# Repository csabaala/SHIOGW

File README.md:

# [SHIOGW](/Hardware/SHIOGW)

DIN rail mount extension board for [Olimex ESP32-GATEWAY](https://www.olimex.com/Products/IoT/ESP32/ESP32-GATEWAY/open-source-hardware).

More [Pictures](/Pictures#assembled-boards) and [Video](https://youtu.be/ds2y22MUNzQ) of the assembled board and extensions.

Example [ESPHome configs](/ESPHome)

## Features

* 12V to 5V step-down converter
* 2 open collector output (50 mA load per channel)
* 2 opto isolated input
* LEDs for output and input status
* 2 sensor input (ds18b20, dht)
* RS-485 interface
* 4 pin JST connector for I2C extensions
* 14 pin IDC connector for direct GPIO access

View [3D model](https://3dviewer.net/#model=https://github.com/csabaala/SHIOGW/blob/main/Hardware/SHIOGW/SHIOGW.wrl)

## Extensions

### [GWHMI](/Hardware/GWHMI)

Control interface for SHIOGW.

* PCB for 128x64 OLED display and control buttons. Fits the 0.96 and 1.3 inch OLED versions.
* Mountable top of the SHIOGW board.
* Connects to SHIOGW's 12 pin IDC connector with a small ribbon cable.
* BTN1 (up) and BTN3 (down) shared with I1 and I2 on SHIOGW main board.

View [3D model](https://3dviewer.net/#model=https://github.com/csabaala/SHIOGW/blob/main/Hardware/GWHMI/GWHMI.wrl)

### [SHIO88E](/Hardware/SHIO88E)

I2C IO extension.

* MCP23017 based
* 8 open collector output (50 mA load per channel)
* 8 opto isolated input
* LEDs for output and input status
* One more I2C connector to connect other device

View [3D model](https://3dviewer.net/#https://github.com/csabaala/SHIOGW/blob/main/Hardware/SHIO88E/SHIO88E.wrl)

### [LRMNT](/Hardware/LRMNT)

Adapter PCB to mount [Heltec LoRa 32 V3](https://heltec.org/project/wifi-lora-32-v3/) module to SHIOGW board.

* 2 extra open collector output (50 mA load per channel)
* 4 extra opto isolated input

View [3D model](https://3dviewer.net/#https://github.com/csabaala/SHIOGW/blob/main/Hardware/LRMNT/LRMNT.wrl)

### [SHIOADS](/Hardware/SHIOADS)

Din rail mount breakout board for ADS1115 module.

* On board voltage divider resistors (R1 - R8)
* Solder jumpers to set I2C address (JP1 - JP4)

View [3D model](https://3dviewer.net/#https://github.com/csabaala/SHIOGW/blob/main/Hardware/SHIOADS/SHIOADS.wrl)

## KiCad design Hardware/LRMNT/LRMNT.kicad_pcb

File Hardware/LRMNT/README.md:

# Assembly information
## 12V power source
To activate the additional digital input and output channels, connect the power source to the H5 header.
You can connect to the SHIOGW H10 connector using a JST cable.

## Using input channel as ADC
You can soldering the input channels (I3 - I5) to use as ADC (Analog to Digital Converter) input.
To enable ADC reading solder the following parts (for example for I3 channel):

* R1: 0 ohm
* R5: 0 ohm (to bypass OP1)
* R3: Voltage divider high resistor 
* R4: Voltage divider low resistor 
* C5: 100 nF capacitor

Do not solder:

* OP1
* C1

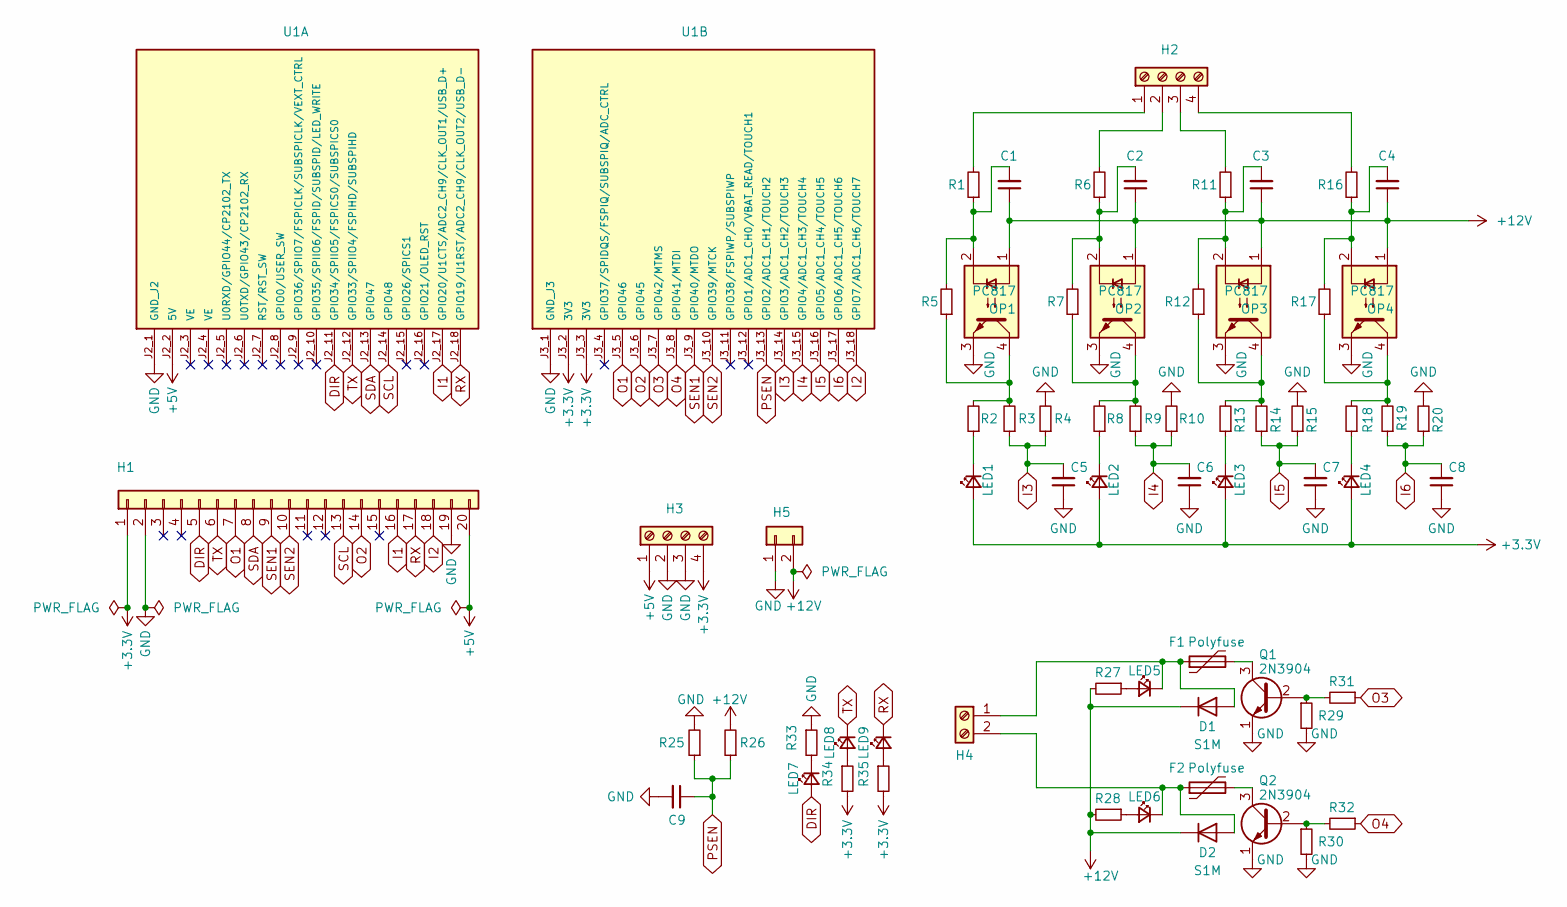
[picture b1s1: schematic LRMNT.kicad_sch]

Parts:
C1, C2, C3, C4: C_Small; C_0805_2012Metric_Pad1.18x1.45mm_HandSolder; LCSC C1710
C5, C6, C7, C8, C9: C_Small; C_0805_2012Metric_Pad1.18x1.45mm_HandSolder; LCSC C49678
D1, D2: S1M; D_SMA; LCSC C412437
F1, F2: Polyfuse; Fuse_1206_3216Metric_Pad1.42x1.75mm_HandSolder; LCSC C2830235
H1: Conn_01x20; PinHeader_1x20_P2.54mm_Vertical
H2, H3: Screw_Terminal_01x04; PhoenixContact_MCV_1,5_4-G-3.5_1x04_P3.50mm_Vertical
H4: Screw_Terminal_01x02; PhoenixContact_MCV_1,5_2-G-3.5_1x02_P3.50mm_Vertical
H5: Conn_01x02; PinHeader_1x02_P2.54mm_Vertical
LED1, LED2, LED3, LED4, LED5, LED6: LED_Small; LED_0805_2012Metric_Pad1.15x1.40mm_HandSolder; LCSC C84256
LED7, LED8: LED_Small; LED_0805_2012Metric_Pad1.15x1.40mm_HandSolder; LCSC C2297
LED9: LED_Small; LED_0805_2012Metric_Pad1.15x1.40mm_HandSolder; LCSC C2296
OP1, OP2, OP3, OP4: PC817; PC817_custom
Q1, Q2: 2N3904; TO-92_HandSolder
R1, R2, R6, R8, R11, R13, R16, R18, R19, R25, R26: R_Small; R_0805_2012Metric_Pad1.20x1.40mm_HandSolder; LCSC C17520
R3, R4, R5, R7, R9, R10, R12, R14, R15, R17, R20: R_Small; R_0805_2012Metric_Pad1.20x1.40mm_HandSolder
R27, R28, R29, R30, R33, R34, R35: R_Small; R_0805_2012Metric_Pad1.20x1.40mm_HandSolder; LCSC C17414
R31, R32: R_Small; R_0805_2012Metric_Pad1.20x1.40mm_HandSolder; LCSC C17513
U1: WIFI_KIT_32__V3_; MODULE_WIFI_KIT_32__V3_; PARTREV Rev 1.1

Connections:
+3.3V: H1.1, H3.4, LED1.2 (A), LED2.2 (A), LED3.2 (A), LED4.2 (A), R34.2, R35.2, U1.J3_2 (3V3), U1.J3_3 (3V3)
+5V: H1.20, H3.1, U1.J2_2 (5V)
+12V: C1.1, C2.1, C3.1, C4.1, D1.1 (K), D2.1 (K), H5.2, OP1.1, OP2.1, OP3.1, OP4.1, R26.2, R27.2, R28.2
DIR: H1.5, LED7.2 (A), U1.J2_11 (GPIO34/SPIIO5/FSPICS0/SUBSPICS0)
GND: C5.1, C6.1, C7.1, C8.1, C9.2, H1.2, H1.19, H3.2, H3.3, H5.1, OP1.3, OP2.3, OP3.3, OP4.3, Q1.1 (E), Q2.1 (E), R4.2, R10.2, R15.2, R20.2, R25.2, R29.2, R30.2, R33.1, U1.J2_1 (GND_J2), U1.J3_1 (GND_J3); also elsewhere on the board
I1: H1.16, U1.J2_17 (GPIO20/U1CTS/ADC2_CH9/CLK_OUT1/USB_D+)
I2: H1.18, U1.J3_18 (GPIO7/ADC1_CH6/TOUCH7)
I3: C5.2, R3.1, R4.1, U1.J3_14 (GPIO3/ADC1_CH2/TOUCH3)
I4: C6.2, R9.1, R10.1, U1.J3_15 (GPIO4/ADC1_CH3/TOUCH4)
I5: C7.2, R14.1, R15.1, U1.J3_16 (GPIO5/ADC1_CH4/TOUCH5)
I6: C8.2, R19.1, R20.1, U1.J3_17 (GPIO6/ADC1_CH5/TOUCH6)
unnamed: C1.2, OP1.2, R1.1, R5.2
unnamed: C2.2, OP2.2, R6.1, R7.2
unnamed: C3.2, OP3.2, R11.1, R12.2
unnamed: C4.2, OP4.2, R16.1, R17.2
unnamed: D1.2 (A), F1.1, H4.1, LED5.1 (K)
unnamed: D2.2 (A), F2.1, H4.2, LED6.1 (K)
unnamed: H2.1, R1.2
unnamed: H2.2, R6.2
unnamed: H2.3, R11.2
unnamed: H2.4, R16.2
unnamed: LED1.1 (K), R2.1
unnamed: LED2.1 (K), R8.1
unnamed: LED3.1 (K), R13.1
unnamed: LED4.1 (K), R18.1
unnamed: LED5.2 (A), R27.1
unnamed: LED6.2 (A), R28.1
unnamed: LED7.1 (K), R33.2
unnamed: LED8.2 (A), R34.1
unnamed: LED9.2 (A), R35.1
unnamed: OP1.4, R2.2, R3.2, R5.1
unnamed: OP2.4, R7.1, R8.2, R9.2
unnamed: OP3.4, R12.1, R13.2, R14.2
unnamed: OP4.4, R17.1, R18.2, R19.2
unnamed: Q1.2 (B), R29.1, R31.2
unnamed: F1.2, Q1.3 (C)
unnamed: Q2.2 (B), R30.1, R32.2
unnamed: F2.2, Q2.3 (C)
O1: H1.7, U1.J3_5 (GPIO46)
O2: H1.14, U1.J3_6 (GPIO45)
O3: R31.1, U1.J3_7 (GPIO42/MTMS)
O4: R32.1, U1.J3_8 (GPIO41/MTDI)
PSEN: C9.1, R25.1, R26.1, U1.J3_13 (GPIO2/ADC1_CH1/TOUCH2)
RX: H1.17, LED9.1 (K), U1.J2_18 (GPIO19/U1RST/ADC2_CH9/CLK_OUT2/USB_D-)
SCL: H1.13, U1.J2_14 (GPIO48)
SDA: H1.8, U1.J2_13 (GPIO47)
SEN1: H1.9, U1.J3_9 (GPIO40/MTDO)
SEN2: H1.10, U1.J3_10 (GPIO39/MTCK)
TX: H1.6, LED8.1 (K), U1.J2_12 (GPIO33/SPIIO4/FSPIHD/SUBSPIHD)

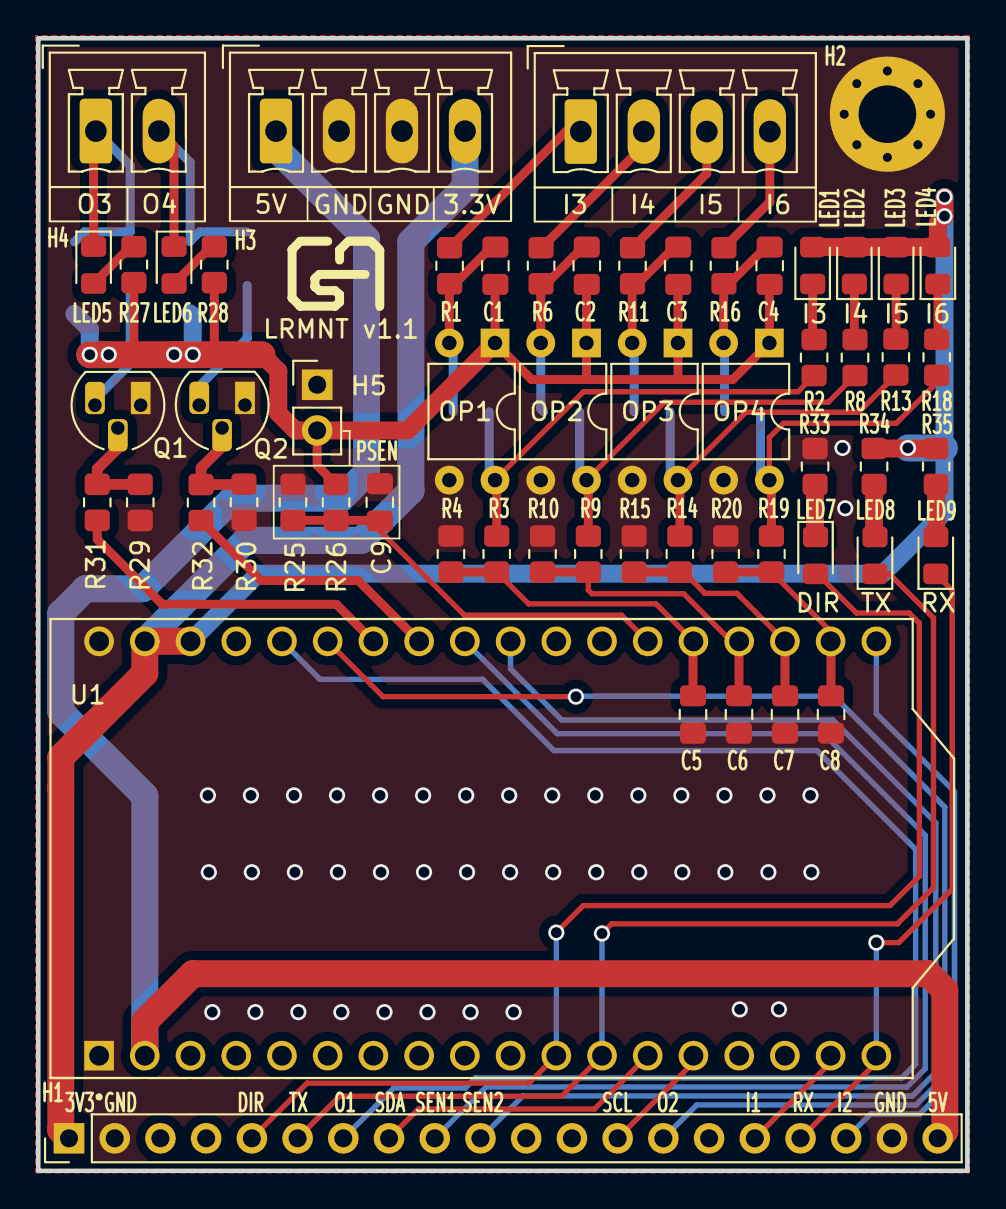
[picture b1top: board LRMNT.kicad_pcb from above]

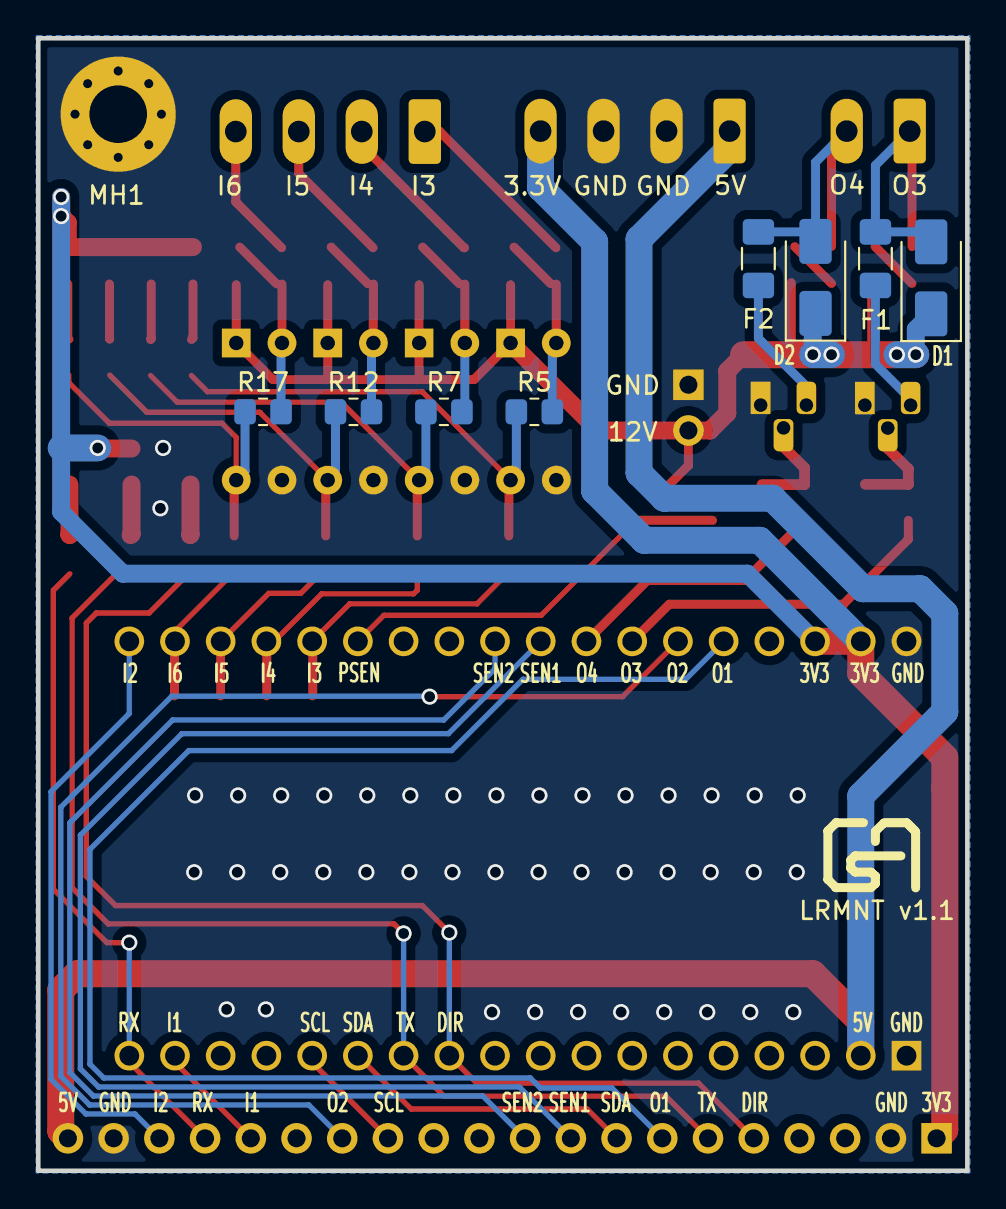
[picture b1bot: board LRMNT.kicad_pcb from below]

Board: 2 copper layers, 51.6 x 62.9 mm, 66 parts (8 on the bottom side), 49 nets.

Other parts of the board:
MH1: MountingHole_Pad; MountingHole_3.2mm_M3_Pad_Via

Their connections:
GND: MH1.1; also elsewhere on the board

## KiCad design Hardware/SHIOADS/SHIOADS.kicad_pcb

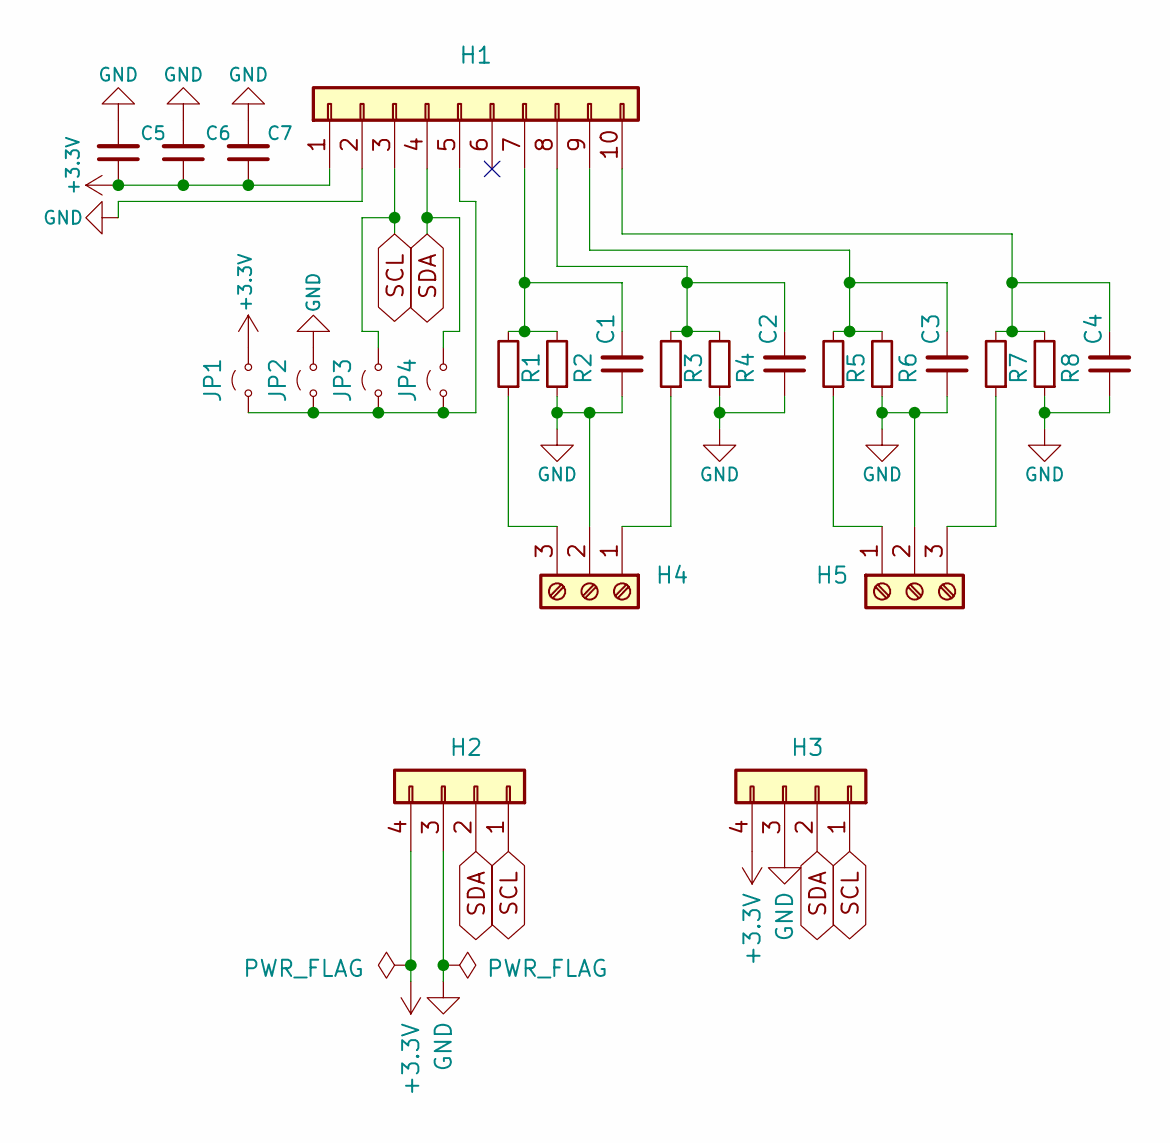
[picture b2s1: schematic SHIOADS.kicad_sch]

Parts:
C1, C2, C3, C4: C_Small; C_0805_2012Metric_Pad1.18x1.45mm_HandSolder; LCSC C1710
C5, C6: C_Small; C_1206_3216Metric_Pad1.33x1.80mm_HandSolder; LCSC C50254
C7: C_Small; C_0805_2012Metric_Pad1.18x1.45mm_HandSolder; LCSC C49678
H1: Conn_01x10; PinSocket_1x10_P2.54mm_Vertical
H2, H3: Conn_01x04; JST_XH_B4B-XH-A_1x04_P2.50mm_Vertical
H4, H5: Screw_Terminal_01x03; TerminalBlock_MSTB 2,5 3-G-5,08_v3
JP1, JP2, JP3, JP4: Jumper_2_Small_Open; SolderJumper-2_P1.3mm_Open_RoundedPad1.0x1.5mm
R1, R3, R5, R7: R_Small; R_0805_2012Metric_Pad1.20x1.40mm_HandSolder; LCSC C17414
R2, R4, R6, R8: R_Small; R_0805_2012Metric_Pad1.20x1.40mm_HandSolder; LCSC C17513

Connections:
+3.3V: C5.1, C6.1, C7.1, H1.1, H2.4, H3.4, JP1.2 (B)
GND: C1.1, C2.1, C3.1, C4.1, C5.2, C6.2, C7.2, H1.2, H2.3, H3.3, H4.2, H5.2, JP2.2 (B), R2.1, R4.1, R6.1, R8.1
unnamed: H1.5, JP1.1 (A), JP2.1 (A), JP3.1 (A), JP4.1 (A)
unnamed: C1.2, H1.7, R1.2, R2.2
unnamed: C2.2, H1.8, R3.2, R4.2
unnamed: C3.2, H1.9, R5.2, R6.2
unnamed: C4.2, H1.10, R7.2, R8.2
unnamed: H4.1, R3.1
unnamed: H4.3, R1.1
unnamed: H5.1, R5.1
unnamed: H5.3, R7.1
SCL: H1.3, H2.1, H3.1, JP3.2 (B)
SDA: H1.4, H2.2, H3.2, JP4.2 (B)

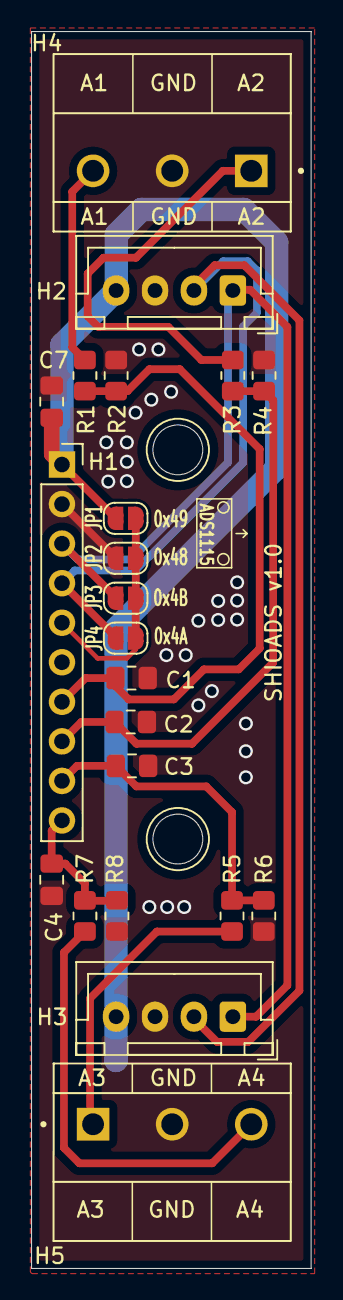
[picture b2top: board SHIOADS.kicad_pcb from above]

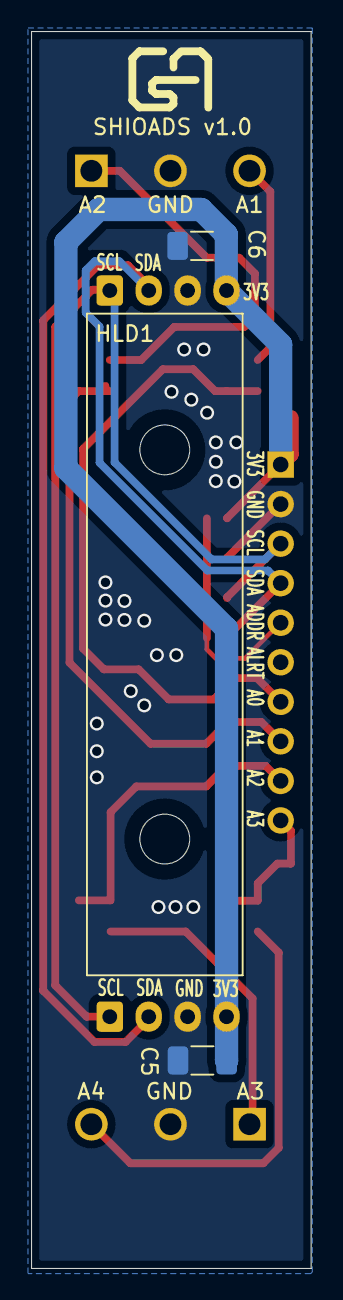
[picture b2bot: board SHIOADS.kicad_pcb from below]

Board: 2 copper layers, 18.0 x 79.5 mm, 25 parts (2 on the bottom side), 13 nets.

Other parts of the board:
HLD1: DINRailAdapter_3xM3_PhoenixContact_1201578

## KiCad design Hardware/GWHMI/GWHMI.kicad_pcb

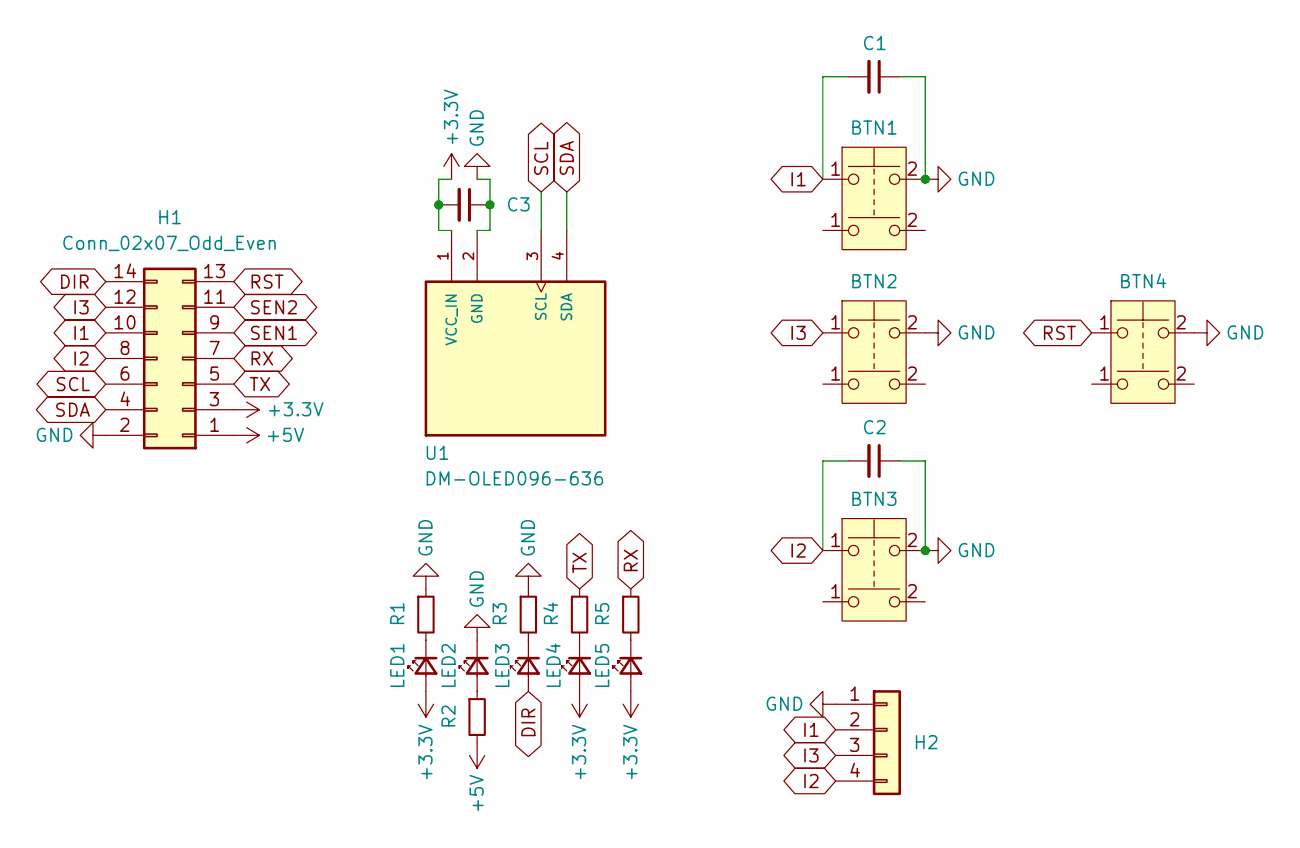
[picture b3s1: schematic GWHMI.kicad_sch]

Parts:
BTN1, BTN2, BTN3, BTN4: SW_Push_Dual; SW_SPST_PTS645_handsolder
C1, C2, C3: C_Small; C_0805_2012Metric_Pad1.18x1.45mm_HandSolder; LCSC C49678
H1: Conn_02x07_Odd_Even; PinHeader_2x07_P2.54mm_Vertical
H2: Conn_01x04; PinHeader_1x04_P2.54mm_Vertical
LED1, LED5: LED_Small; LED_0805_2012Metric_Pad1.15x1.40mm_HandSolder; LCSC C2296
LED2: LED_Small; LED_0805_2012Metric_Pad1.15x1.40mm_HandSolder; LCSC C84256
LED3, LED4: LED_Small; LED_0805_2012Metric_Pad1.15x1.40mm_HandSolder; LCSC C2297
R1: R_Small; R_0805_2012Metric_Pad1.20x1.40mm_HandSolder; LCSC C17520
R2: R_Small; R_0805_2012Metric_Pad1.20x1.40mm_HandSolder; LCSC C17661
R3, R4, R5: R_Small; R_0805_2012Metric_Pad1.20x1.40mm_HandSolder; LCSC C17414
U1: DM-OLED096-636; display_oled_128x64_i2c; PARTREV 2018-09-10

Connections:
+3.3V: C3.2, H1.3, LED1.2 (A), LED4.2 (A), LED5.2 (A), U1.1 (VCC_IN)
+5V: H1.1, R2.2
DIR: H1.14, LED3.2 (A)
GND: BTN1.2, BTN2.2, BTN3.2, BTN4.2, C1.1, C2.1, C3.1, H1.2, H2.1, LED2.1 (K), R1.1, R3.1, U1.2 (GND)
I1: BTN1.1, C1.2, H1.10, H2.2
I2: BTN3.1, C2.2, H1.8, H2.4
I3: BTN2.1, H1.12, H2.3
unnamed: LED1.1 (K), R1.2
unnamed: LED2.2 (A), R2.1
unnamed: LED3.1 (K), R3.2
unnamed: LED4.1 (K), R4.2
unnamed: LED5.1 (K), R5.2
RST: BTN4.1, H1.13
RX: H1.7, R5.1
SCL: H1.6, U1.3 (SCL)
SDA: H1.4, U1.4 (SDA)
SEN1: H1.9
SEN2: H1.11
TX: H1.5, R4.1

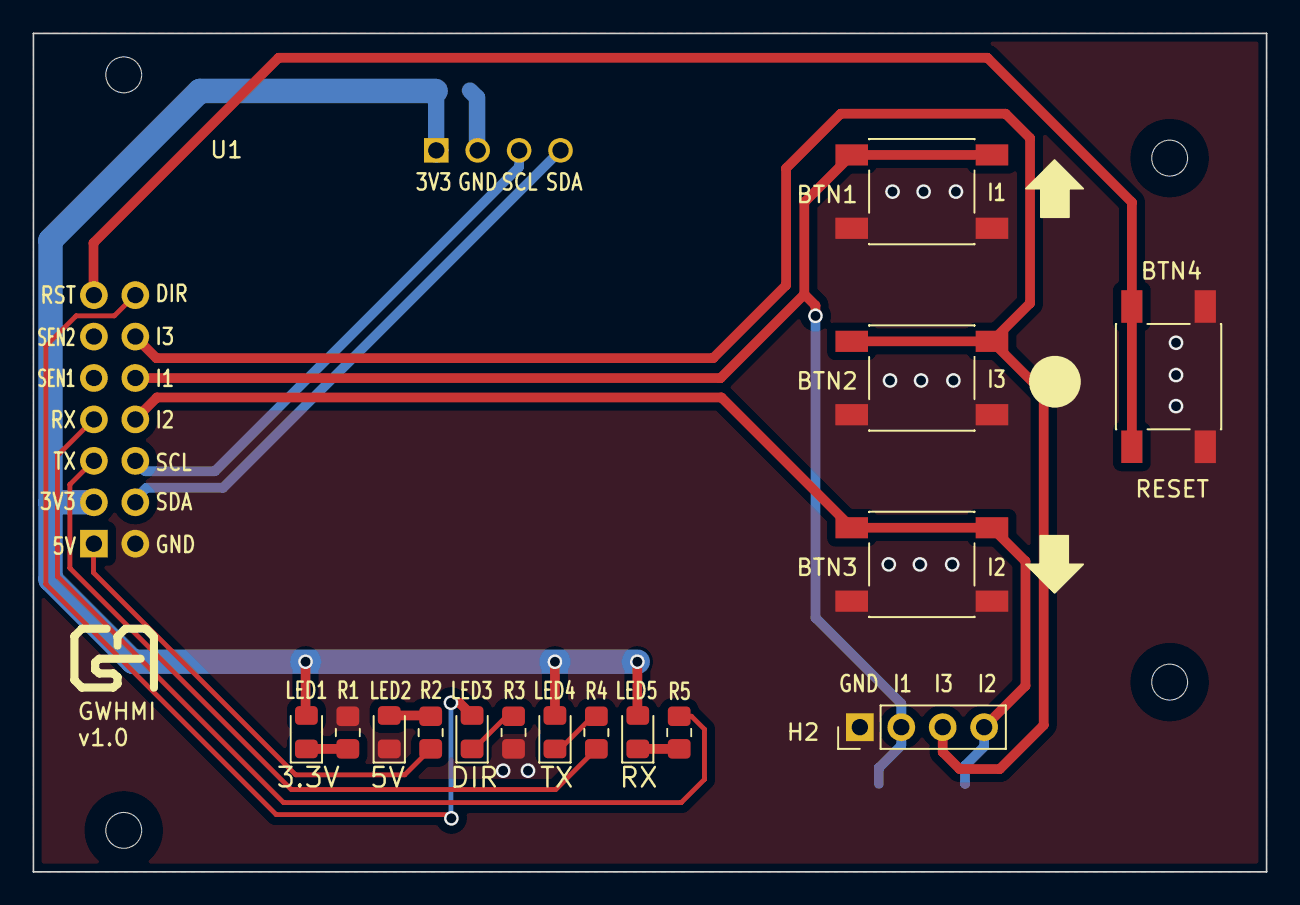
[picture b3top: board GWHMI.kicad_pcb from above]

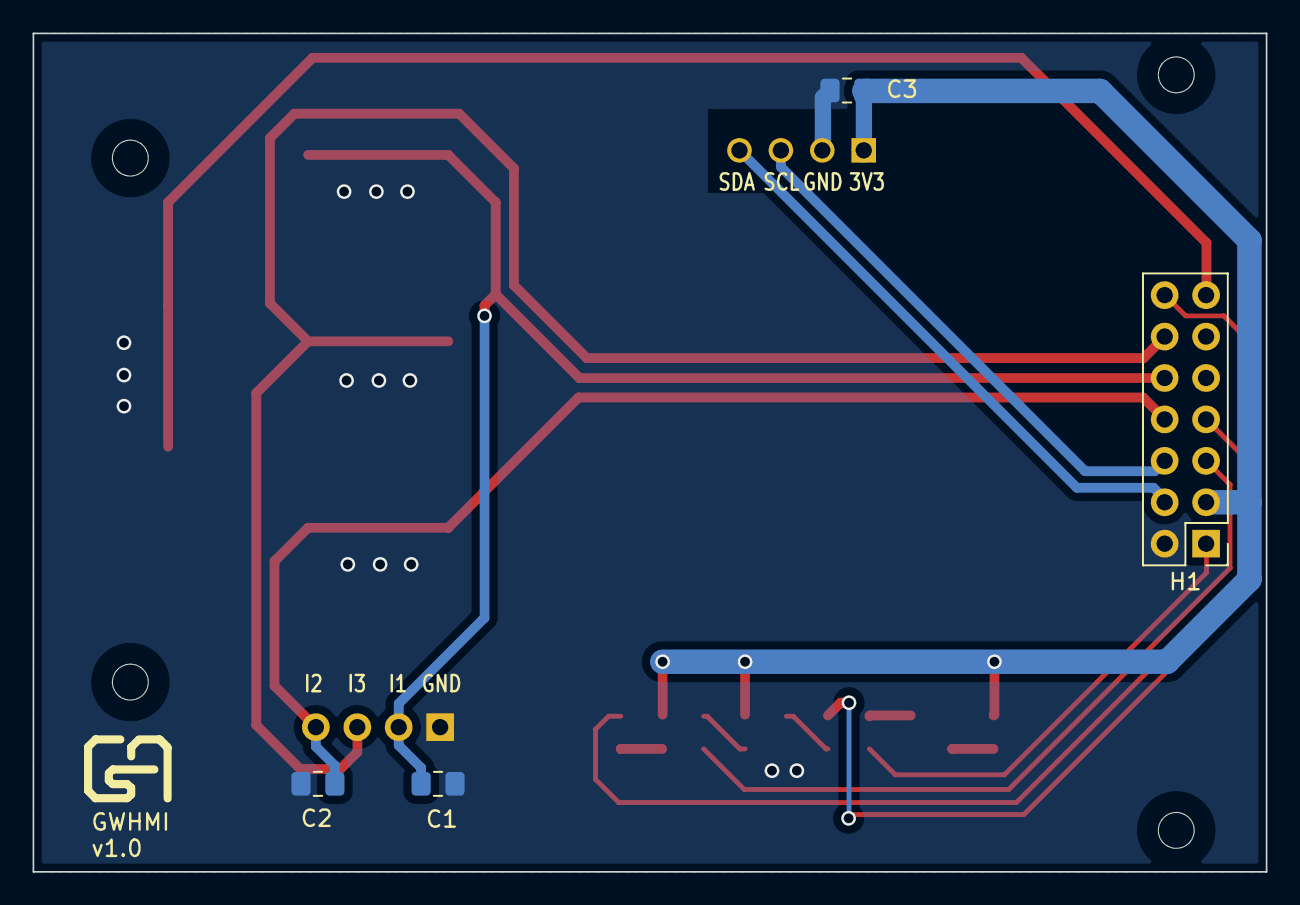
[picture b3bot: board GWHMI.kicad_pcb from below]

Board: 2 copper layers, 75.6 x 51.4 mm, 20 parts (4 on the bottom side), 17 nets.

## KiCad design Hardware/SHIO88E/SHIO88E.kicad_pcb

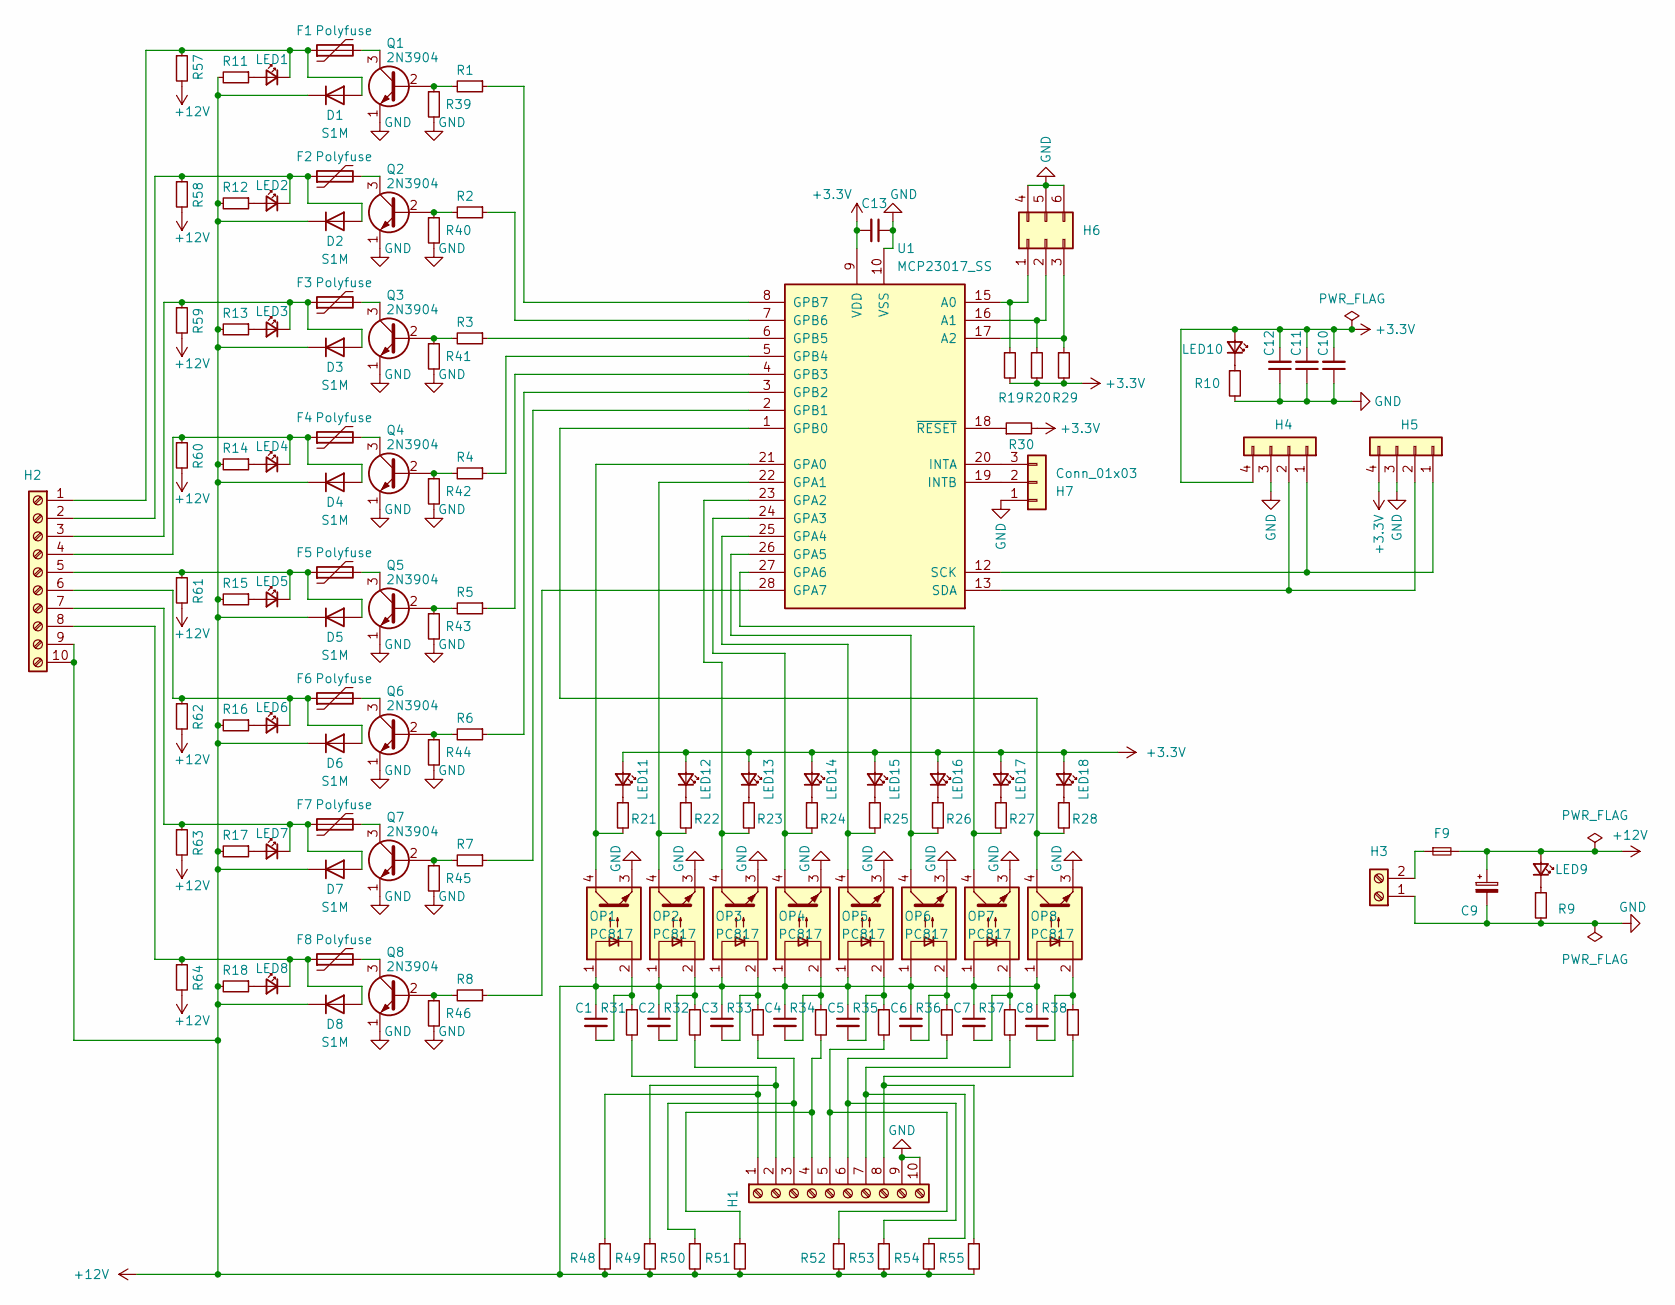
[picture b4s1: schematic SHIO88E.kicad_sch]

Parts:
C1, C2, C3, C4, C5, C6, C7, C8: C_Small; C_0805_2012Metric_Pad1.18x1.45mm_HandSolder; LCSC C1710
C9: C_Polarized_Small; CP_Radial_D10.0mm_P5.00mm
C10, C11, C12: C_Small; C_1206_3216Metric_Pad1.33x1.80mm_HandSolder; LCSC C13585
C13: C_Small; C_0805_2012Metric_Pad1.18x1.45mm_HandSolder; LCSC C49678
D1, D2, D3, D4, D5, D6, D7, D8: S1M; D_SMA
F1, F2, F3, F4, F5, F6, F7, F8: Polyfuse; Fuse_1206_3216Metric_Pad1.42x1.75mm_HandSolder
F9: Fuse_Small; FUSE_holder
H1, H2: Screw_Terminal_01x10; MSTB 2,5-10-G-5,08_custom
H3: Screw_Terminal_01x02; MSTB 2,5-2-G-5,08
H4, H5: Conn_01x04; JST_XH_B4B-XH-A_1x04_P2.50mm_Vertical
H6: Conn_02x03_Top_Bottom; PinHeader_2x03_P2.54mm_Vertical
H7: Conn_01x03; JST_XH_B3B-XH-A_1x03_P2.50mm_Vertical
LED1, LED2, LED3, LED4, LED5, LED6, LED7, LED8, LED11, LED12, LED13, LED14, LED15, LED16, LED17, LED18: LED_Small; LED_0805_2012Metric_Pad1.15x1.40mm_HandSolder; LCSC C84256
LED9, LED10: LED_Small; LED_0805_2012Metric_Pad1.15x1.40mm_HandSolder; LCSC C2296
OP1, OP2, OP3, OP4, OP5, OP6, OP7, OP8: PC817; PC817_custom
Q1, Q2, Q3, Q4, Q5, Q6, Q7, Q8: 2N3904; TO-92_HandSolder
R1, R2, R3, R4, R5, R6, R7, R8: R_Small; R_0805_2012Metric_Pad1.20x1.40mm_HandSolder; LCSC C17513
R9, R11, R12, R13, R14, R15, R16, R17, R18, R19, R20, R29, R30: R_Small; R_0805_2012Metric_Pad1.20x1.40mm_HandSolder; LCSC C17414
R10, R21, R22, R23, R24, R25, R26, R27, R28, R31, R32, R33, R34, R35, R36, R37, R38: R_Small; R_0805_2012Metric_Pad1.20x1.40mm_HandSolder; LCSC C17520
R39, R40, R41, R42, R43, R44, R45, R46, R48, R49, R50, R51, R52, R53, R54, R55, R57, R58, R59, R60, R61, R62, R63, R64: R_Small; R_0805_2012Metric_Pad1.20x1.40mm_HandSolder
U1: MCP23017_SS; SSOP-28_5.3x10.2mm_P0.65mm; LCSC C558584

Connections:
+3.3V: C10.2, C11.2, C12.2, C13.2, H4.4, H5.4, LED10.2 (A), LED11.2 (A), LED12.2 (A), LED13.2 (A), LED14.2 (A), LED15.2 (A), LED16.2 (A), LED17.2 (A), LED18.2 (A), R19.2, R20.2, R29.2, R30.2, U1.9 (VDD)
+12V: C1.1, C2.1, C3.1, C4.1, C5.1, C6.1, C7.1, C8.1, C9.1, D1.1 (K), D2.1 (K), D3.1 (K), D4.1 (K), D5.1 (K), D6.1 (K), D7.1 (K), D8.1 (K), F9.2, H2.9, H2.10, LED9.2 (A), OP1.1, OP2.1, OP3.1, OP4.1, OP5.1, OP6.1, OP7.1, OP8.1, R11.2, R12.2, R13.2, R14.2, R15.2, R16.2, R17.2, R18.2, R48.2, R49.2, R50.2, R51.2, R52.2, R53.2, R54.2, R55.2, R57.2, R58.2, R59.2, R60.2, R61.2, R62.2, R63.2, R64.2
GND: C9.2, C10.1, C11.1, C12.1, C13.1, H1.9, H1.10, H3.1, H4.3, H5.3, H6.4, H6.5, H6.6, H7.1, OP1.3, OP2.3, OP3.3, OP4.3, OP5.3, OP6.3, OP7.3, OP8.3, Q1.1 (E), Q2.1 (E), Q3.1 (E), Q4.1 (E), Q5.1 (E), Q6.1 (E), Q7.1 (E), Q8.1 (E), R9.2, R10.2, R39.2, R40.2, R41.2, R42.2, R43.2, R44.2, R45.2, R46.2, U1.10 (VSS)
unnamed: C1.2, OP1.2, R31.1
unnamed: C2.2, OP2.2, R32.1
unnamed: C3.2, OP3.2, R33.1
unnamed: C4.2, OP4.2, R34.1
unnamed: C5.2, OP5.2, R35.1
unnamed: C6.2, OP6.2, R36.1
unnamed: C7.2, OP7.2, R37.1
unnamed: C8.2, OP8.2, R38.1
unnamed: D1.2 (A), F1.1, H2.1, LED1.1 (K), R57.1
unnamed: D2.2 (A), F2.1, H2.2, LED2.1 (K), R58.1
unnamed: D3.2 (A), F3.1, H2.3, LED3.1 (K), R59.1
unnamed: D4.2 (A), F4.1, H2.4, LED4.1 (K), R60.1
unnamed: D5.2 (A), F5.1, H2.5, LED5.1 (K), R61.1
unnamed: D6.2 (A), F6.1, H2.6, LED6.1 (K), R62.1
unnamed: D7.2 (A), F7.1, H2.7, LED7.1 (K), R63.1
unnamed: D8.2 (A), F8.1, H2.8, LED8.1 (K), R64.1
unnamed: H1.1, R31.2, R48.1
unnamed: H1.2, R32.2, R49.1
unnamed: H1.3, R33.2, R50.1
unnamed: H1.4, R34.2, R51.1
unnamed: H1.5, R35.2, R52.1
unnamed: H1.6, R36.2, R53.1
unnamed: H1.7, R37.2, R54.1
unnamed: H1.8, R38.2, R55.1
unnamed: F9.1, H3.2
unnamed: H4.1, H5.1, U1.12 (SCK)
unnamed: H4.2, H5.2, U1.13 (SDA)
unnamed: H6.1, R19.1, U1.15 (A0)
unnamed: H6.2, R20.1, U1.16 (A1)
unnamed: H6.3, R29.1, U1.17 (A2)
unnamed: H7.2, U1.19 (INTB)
unnamed: H7.3, U1.20 (INTA)
unnamed: LED1.2 (A), R11.1
unnamed: LED2.2 (A), R12.1
unnamed: LED3.2 (A), R13.1
unnamed: LED4.2 (A), R14.1
unnamed: LED5.2 (A), R15.1
unnamed: LED6.2 (A), R16.1
unnamed: LED7.2 (A), R17.1
unnamed: LED8.2 (A), R18.1
unnamed: LED9.1 (K), R9.1
unnamed: LED10.1 (K), R10.1
unnamed: LED11.1 (K), R21.1
unnamed: LED12.1 (K), R22.1
unnamed: LED13.1 (K), R23.1
unnamed: LED14.1 (K), R24.1
unnamed: LED15.1 (K), R25.1
unnamed: LED16.1 (K), R26.1
unnamed: LED17.1 (K), R27.1
unnamed: LED18.1 (K), R28.1
unnamed: Q1.2 (B), R1.2, R39.1
unnamed: F1.2, Q1.3 (C)
unnamed: Q2.2 (B), R2.2, R40.1
unnamed: F2.2, Q2.3 (C)
unnamed: Q3.2 (B), R3.2, R41.1
unnamed: F3.2, Q3.3 (C)
unnamed: Q4.2 (B), R4.2, R42.1
unnamed: F4.2, Q4.3 (C)
unnamed: Q5.2 (B), R5.2, R43.1
unnamed: F5.2, Q5.3 (C)
unnamed: Q6.2 (B), R6.2, R44.1
unnamed: F6.2, Q6.3 (C)
unnamed: Q7.2 (B), R7.2, R45.1
unnamed: F7.2, Q7.3 (C)
unnamed: Q8.2 (B), R8.2, R46.1
unnamed: F8.2, Q8.3 (C)
unnamed: OP1.4, R21.2, U1.21 (GPA0)
unnamed: OP2.4, R22.2, U1.22 (GPA1)
unnamed: OP3.4, R23.2, U1.23 (GPA2)
unnamed: OP4.4, R24.2, U1.24 (GPA3)
unnamed: OP5.4, R25.2, U1.25 (GPA4)
unnamed: OP6.4, R26.2, U1.26 (GPA5)
unnamed: OP7.4, R27.2, U1.27 (GPA6)
unnamed: R8.1, U1.28 (GPA7)
unnamed: OP8.4, R28.2, U1.1 (GPB0)
unnamed: R7.1, U1.2 (GPB1)
unnamed: R6.1, U1.3 (GPB2)
unnamed: R5.1, U1.4 (GPB3)
unnamed: R4.1, U1.5 (GPB4)
unnamed: R3.1, U1.6 (GPB5)
unnamed: R2.1, U1.7 (GPB6)
unnamed: R1.1, U1.8 (GPB7)
unnamed: R30.1, U1.18 (~RESET)
